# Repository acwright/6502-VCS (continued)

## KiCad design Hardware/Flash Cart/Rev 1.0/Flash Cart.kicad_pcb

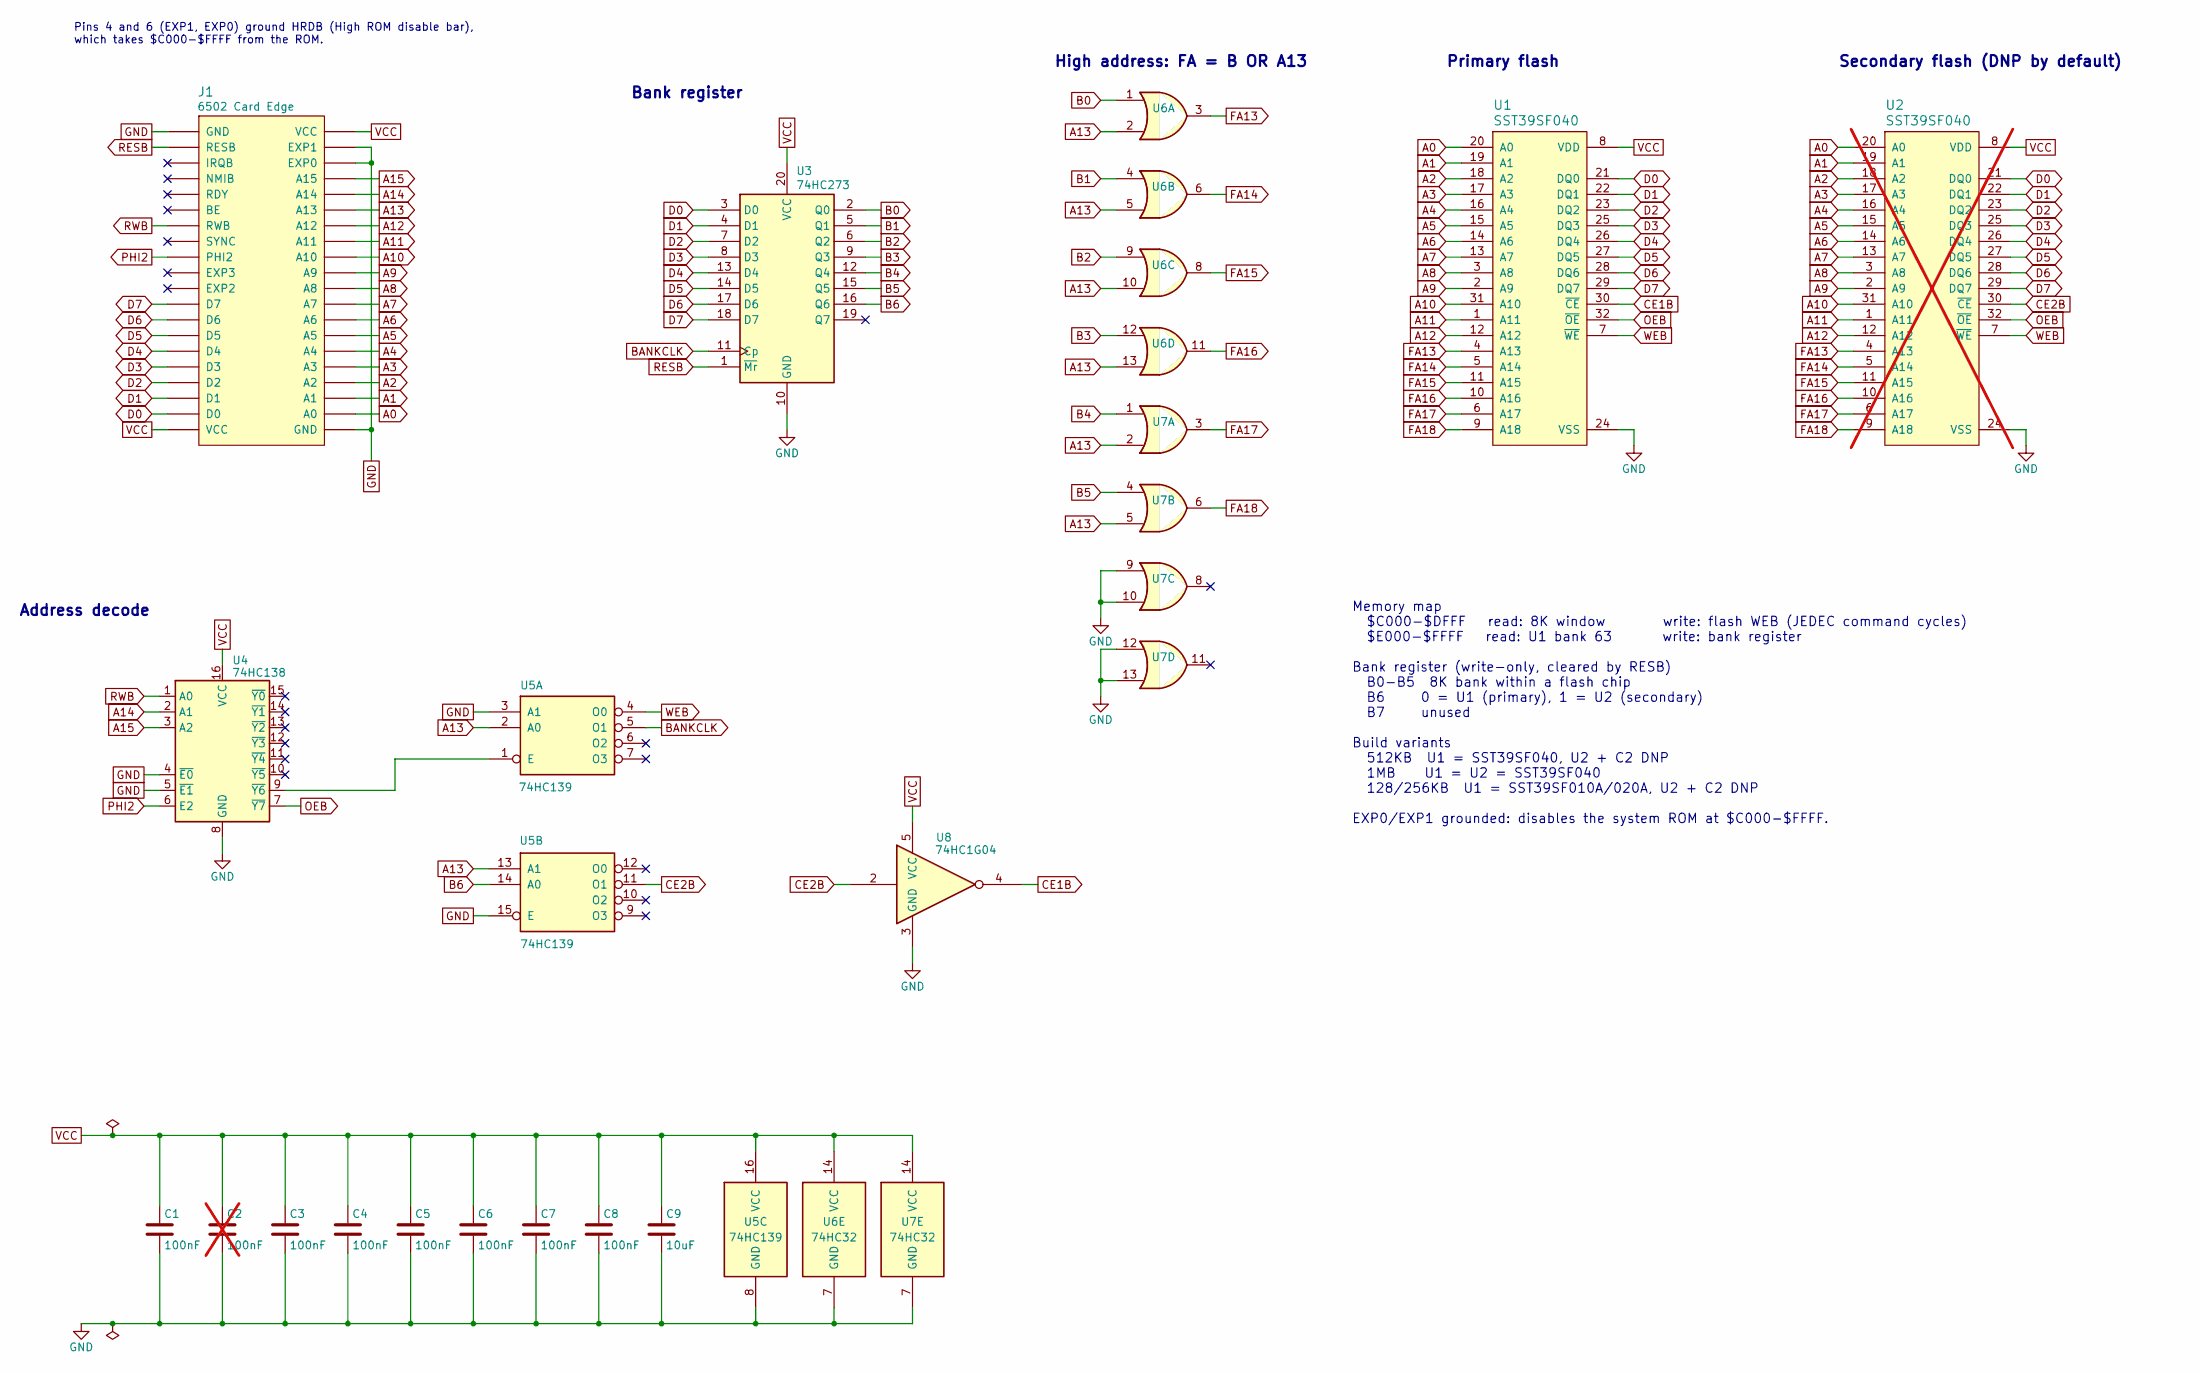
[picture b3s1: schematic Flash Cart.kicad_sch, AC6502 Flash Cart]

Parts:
C1, C3, C4, C5, C6, C7, C8: 100nF; C_0603_1608Metric; Digikey 399-C0603C104K5RACTUCT-ND
C2: 100nF; C_0603_1608Metric; Digikey 399-C0603C104K5RACTUCT-ND; not fitted
C9: 10uF; C_0805_2012Metric; Digikey 311-3502-1-ND
J1: 6502 Card Edge
U1: SST39SF040; TSOP-I-32_11.8x8mm_P0.5mm; Digikey 150-SST39SF040-70-4C-TU-ND
U2: SST39SF040; TSOP-I-32_11.8x8mm_P0.5mm; Digikey 150-SST39SF040-70-4C-TU-ND; not fitted
U3: 74HC273; SOIC-20W_7.5x12.8mm_P1.27mm; Digikey 1727-2795-1-ND
U4: 74HC138; SOIC-16_3.9x9.9mm_P1.27mm; Digikey 1727-2781-1-ND
U5: 74HC139; SOIC-16_3.9x9.9mm_P1.27mm; Digikey 1727-5943-1-ND
U6, U7: 74HC32; SOIC-14_3.9x8.7mm_P1.27mm; Digikey 1727-2797-1-ND
U8: 74HC1G04; SOT-23-5; Digikey 1727-6034-1-ND

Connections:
A0: J1.A0, U1.20 (A0), U2.20 (A0)
A1: J1.A1, U1.19 (A1), U2.19 (A1)
A2: J1.A2, U1.18 (A2), U2.18 (A2)
A3: J1.A3, U1.17 (A3), U2.17 (A3)
A4: J1.A4, U1.16 (A4), U2.16 (A4)
A5: J1.A5, U1.15 (A5), U2.15 (A5)
A6: J1.A6, U1.14 (A6), U2.14 (A6)
A7: J1.A7, U1.13 (A7), U2.13 (A7)
A8: J1.A8, U1.3 (A8), U2.3 (A8)
A9: J1.A9, U1.2 (A9), U2.2 (A9)
A10: J1.A10, U1.31 (A10), U2.31 (A10)
A11: J1.A11, U1.1 (A11), U2.1 (A11)
A12: J1.A12, U1.12 (A12), U2.12 (A12)
A13: J1.A13, U5.2 (A0), U5.13 (A1), U6.2, U6.5, U6.10, U6.13, U7.2, U7.5
A14: J1.A14, U4.2 (A1)
A15: J1.A15, U4.3 (A2)
B0: U3.2 (Q0), U6.1
B1: U3.5 (Q1), U6.4
B2: U3.6 (Q2), U6.9
B3: U3.9 (Q3), U6.12
B4: U3.12 (Q4), U7.1
B5: U3.15 (Q5), U7.4
B6: U3.16 (Q6), U5.14 (A0)
BANKCLK: U3.11 (Cp), U5.5 (O1)
CE1B: U1.30 (~CE), U8.4
CE2B: U2.30 (~CE), U5.11 (O1), U8.2
D0: J1.D0, U1.21 (DQ0), U2.21 (DQ0), U3.3 (D0)
D1: J1.D1, U1.22 (DQ1), U2.22 (DQ1), U3.4 (D1)
D2: J1.D2, U1.23 (DQ2), U2.23 (DQ2), U3.7 (D2)
D3: J1.D3, U1.25 (DQ3), U2.25 (DQ3), U3.8 (D3)
D4: J1.D4, U1.26 (DQ4), U2.26 (DQ4), U3.13 (D4)
D5: J1.D5, U1.27 (DQ5), U2.27 (DQ5), U3.14 (D5)
D6: J1.D6, U1.28 (DQ6), U2.28 (DQ6), U3.17 (D6)
D7: J1.D7, U1.29 (DQ7), U2.29 (DQ7), U3.18 (D7)
FA13: U1.4 (A13), U2.4 (A13), U6.3
FA14: U1.5 (A14), U2.5 (A14), U6.6
FA15: U1.11 (A15), U2.11 (A15), U6.8
FA16: U1.10 (A16), U2.10 (A16), U6.11
FA17: U1.6 (A17), U2.6 (A17), U7.3
FA18: U1.9 (A18), U2.9 (A18), U7.6
GND: C1.2, C2.2, C3.2, C4.2, C5.2, C6.2, C7.2, C8.2, C9.2, J1.EXP0, J1.EXP1, J1.GND, U1.24 (VSS), U2.24 (VSS), U3.10 (GND), U4.4 (~E0), U4.5 (~E1), U4.8 (GND), U5.3 (A1), U5.8 (GND), U5.15 (E), U6.7 (GND), U7.7 (GND), U7.9, U7.10, U7.12, U7.13, U8.3 (GND)
unnamed: U4.9 (~Y6), U5.1 (E)
OEB: U1.32 (~OE), U2.32 (~OE), U4.7 (~Y7)
PHI2: J1.PHI2, U4.6 (E2)
RESB: J1.RESB, U3.1 (~Mr)
RWB: J1.RWB, U4.1 (A0)
VCC: C1.1, C2.1, C3.1, C4.1, C5.1, C6.1, C7.1, C8.1, C9.1, J1.VCC, U1.8 (VDD), U2.8 (VDD), U3.20 (VCC), U4.16 (VCC), U5.16 (VCC), U6.14 (VCC), U7.14 (VCC), U8.5 (VCC)
WEB: U1.7 (~WE), U2.7 (~WE), U5.4 (O0)

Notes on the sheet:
High address: FA = B OR A13
Secondary flash (DNP by default)
Address decode
Memory map $C000-$DFFF read: 8K window write: flash WEB (JEDEC command cycles) $E000-$FFFF read: U1 bank 63 write: bank register Bank register (write-only, cleared by RESB) B0-B5 8K bank within a flash chip B6 0 = U1 (primary), 1 = U2 (secondary) B7 unused Build variants 512KB U1 = SST39SF040, U2 +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
Primary flash
Bank register
Pins 4 and 6 (EXP1, EXP0) ground HRDB (High ROM disable bar), which takes $C000-$FFFF from the ROM.

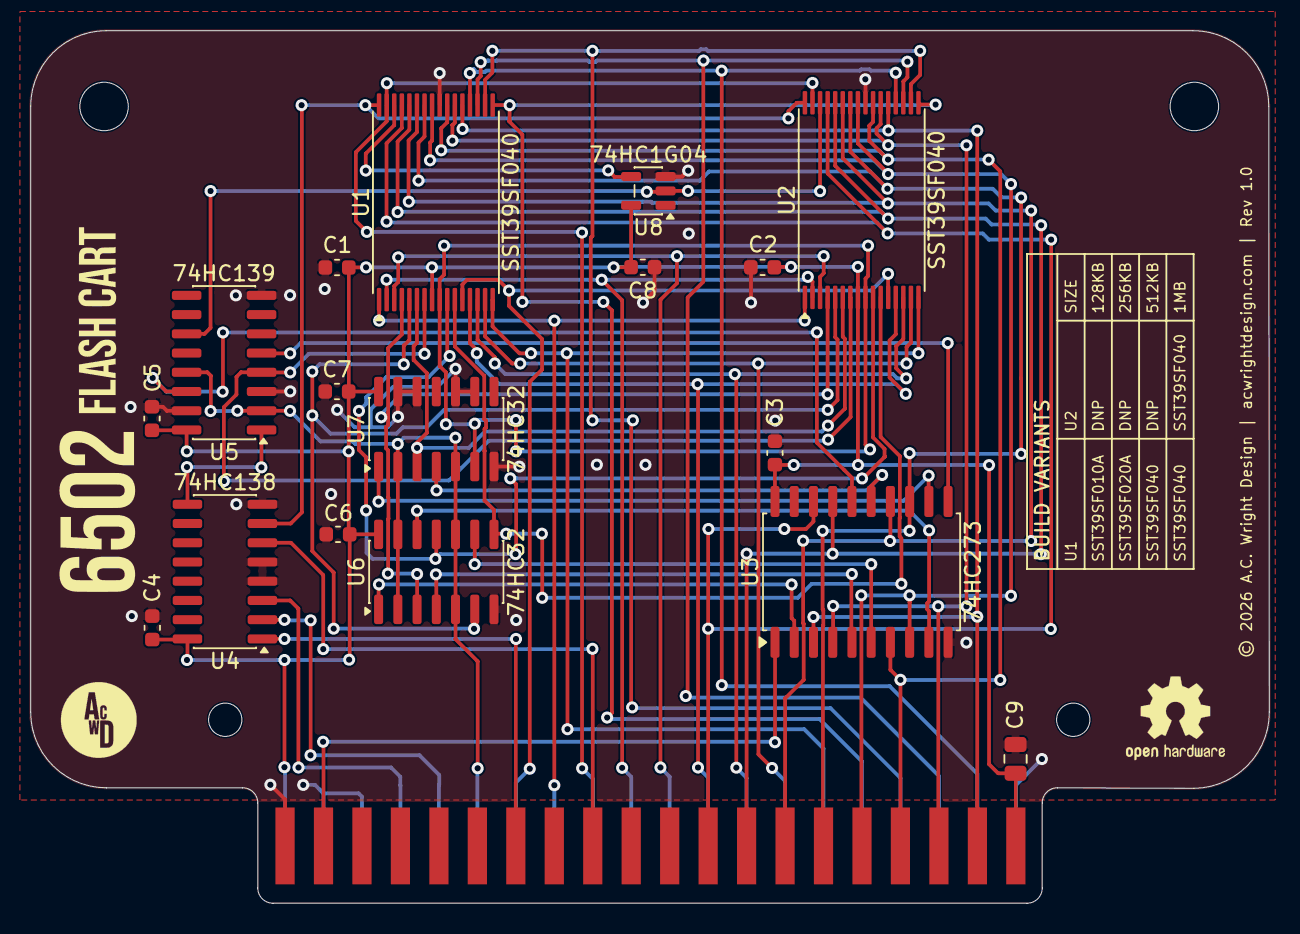
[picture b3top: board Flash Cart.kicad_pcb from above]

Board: 2 copper layers, 81.8 x 57.6 mm, 22 parts (0 on the bottom side), 48 nets.

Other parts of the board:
H1, H2: MountingHole; MountingHole_3.2mm_M3
H3, H4: MountingHole; MountingHole_2.2mm_M2

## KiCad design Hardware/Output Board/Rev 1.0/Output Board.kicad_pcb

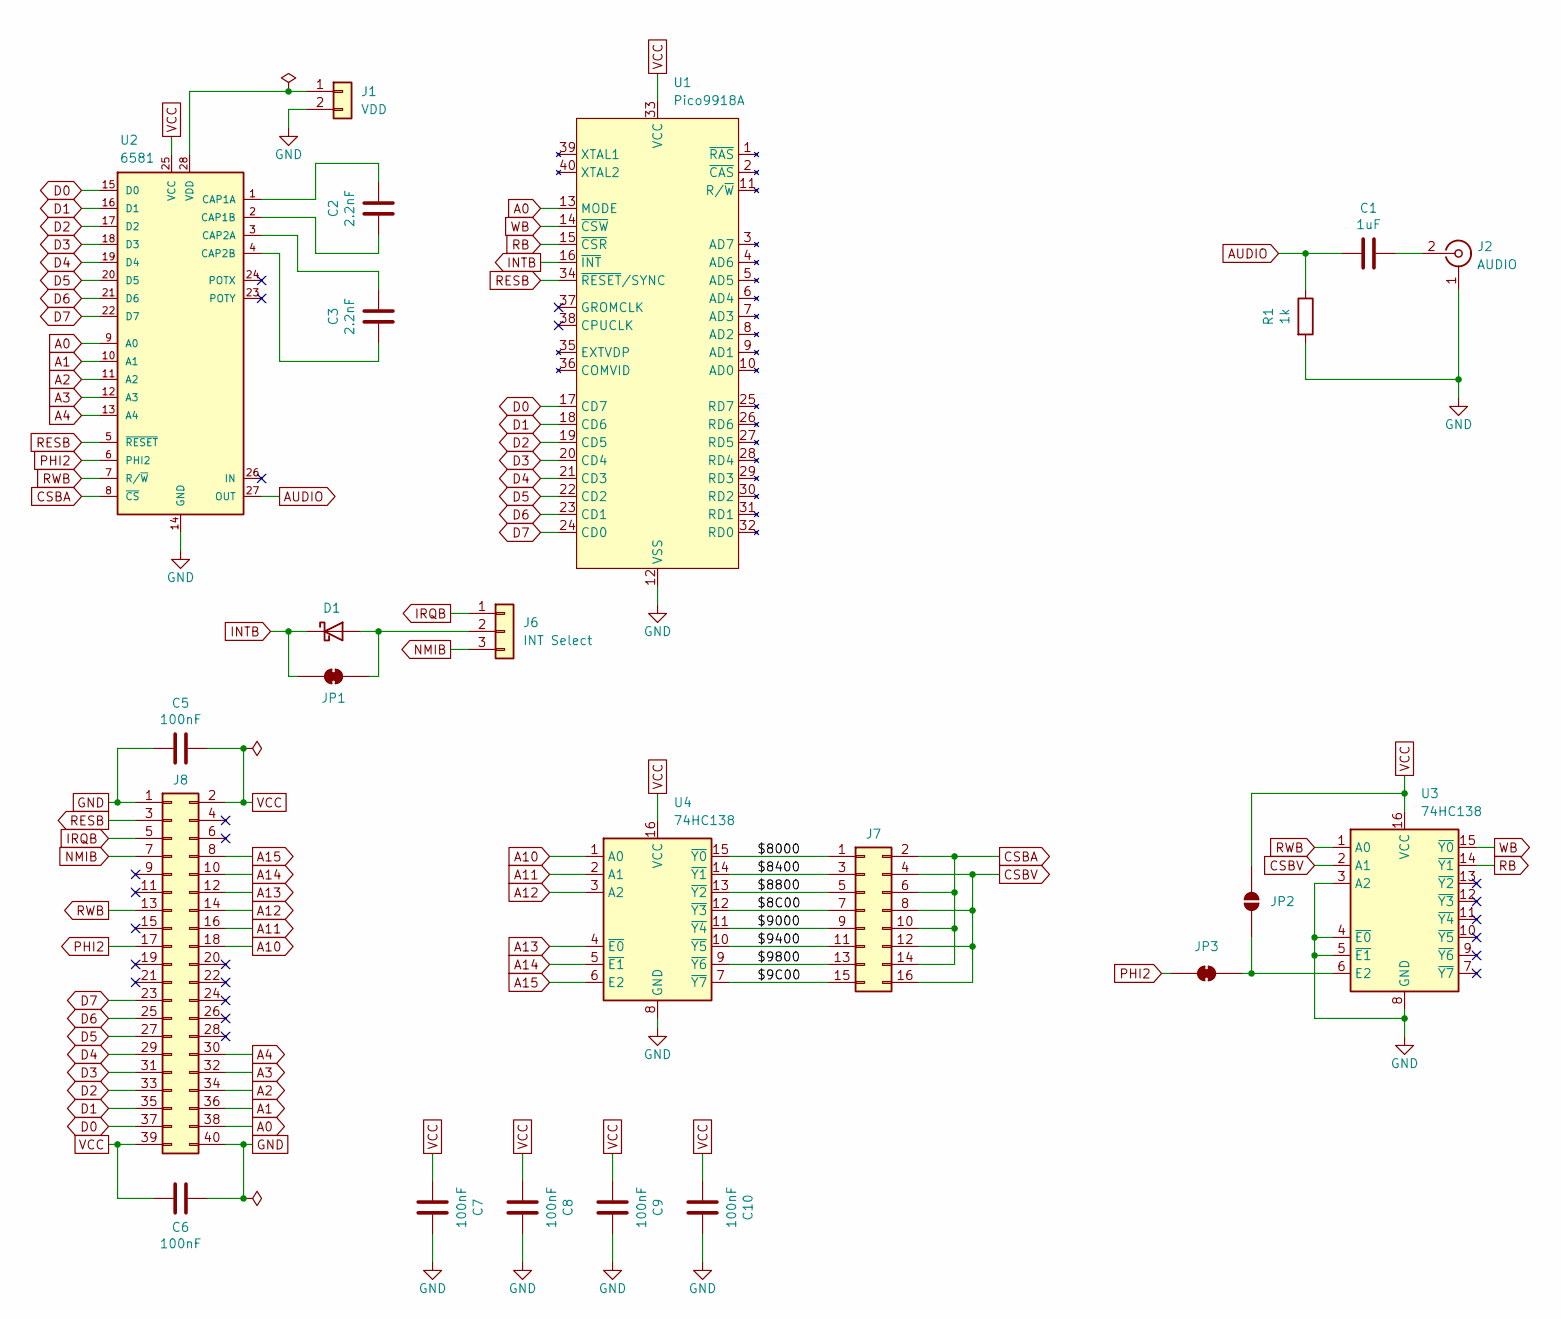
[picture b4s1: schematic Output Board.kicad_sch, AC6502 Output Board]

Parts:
C1: 1uF; C_0805_2012Metric; LCSC C28323
C2, C3: 2.2nF; C_0805_2012Metric; LCSC C28260
C5, C6, C7, C8, C9, C10: 100nF; C_0805_2012Metric; LCSC C49678
D1: 1N914; D_DO-35_SOD27_P7.62mm_Horizontal; Mouser 512-1N914
J1: VDD; JST_XH_B2B-XH-A_1x02_P2.50mm_Vertical; Digikey 455-B2B-XH-A-ND
J2: AUDIO; RCA Jack White; Digikey PJRAN1X1U02X-ND
J6: INT Select; PinHeader_1x03_P2.54mm_Vertical; Mouser 200-TSW14007TS
J7: IO SELECT; PinHeader_2x08_P2.54mm_Vertical; Mouser 649-67996-140HLF
J8: 6502 Bus; 6502 Bus Connector; Mouser 710-61204021621
JP1, JP3: SolderJumper_2_Bridged; SolderJumper-2_P1.3mm_Bridged_RoundedPad1.0x1.5mm
JP2: SolderJumper_2_Open; SolderJumper-2_P1.3mm_Open_RoundedPad1.0x1.5mm
R1: 1k; R_0805_2012Metric; LCSC C17513
U1: Pico9918A; DIP_Socket-40_W11.9mm_W12.7mm_W15.24mm_W17.78mm_W18.5mm_3M_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
U2: 6581; DIP_Socket-28_W11.9mm_W12.7mm_W15.24mm_W17.78mm_W18.5mm_3M_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
U3, U4: 74HC138; SOIC-16_3.9x9.9mm_P1.27mm; LCSC C5602

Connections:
/$8C00: J7.7, U4.12 (~Y3)
/$9C00: J7.15, U4.7 (~Y7)
/$8000: J7.1, U4.15 (~Y0)
/$8400: J7.3, U4.14 (~Y1)
/$8800: J7.5, U4.13 (~Y2)
/$9000: J7.9, U4.11 (~Y4)
/$9400: J7.11, U4.10 (~Y5)
/$9800: J7.13, U4.9 (~Y6)
A0: J8.38, U1.13 (MODE), U2.9 (A0)
A1: J8.36, U2.10 (A1)
A2: J8.34, U2.11 (A2)
A3: J8.32, U2.12 (A3)
A4: J8.30, U2.13 (A4)
A10: J8.18, U4.1 (A0)
A11: J8.16, U4.2 (A1)
A12: J8.14, U4.3 (A2)
A13: J8.12, U4.4 (~E0)
A14: J8.10, U4.5 (~E1)
A15: J8.8, U4.6 (E2)
AUDIO: C1.1, R1.1, U2.27 (OUT)
CSBA: J7.2, J7.6, J7.10, J7.14, U2.8 (~CS)
CSBV: J7.4, J7.8, J7.12, J7.16, U3.2 (A1)
D0: J8.37, U1.17 (CD7), U2.15 (D0)
D1: J8.35, U1.18 (CD6), U2.16 (D1)
D2: J8.33, U1.19 (CD5), U2.17 (D2)
D3: J8.31, U1.20 (CD4), U2.18 (D3)
D4: J8.29, U1.21 (CD3), U2.19 (D4)
D5: J8.27, U1.22 (CD2), U2.20 (D5)
D6: J8.25, U1.23 (CD1), U2.21 (D6)
D7: J8.23, U1.24 (CD0), U2.22 (D7)
GND: C5.2, C6.1, C7.2, C8.2, C9.2, C10.2, J1.2, J2.1 (Ext), J8.1, J8.40, R1.2, U1.12 (VSS), U2.14 (GND), U3.3 (A2), U3.4 (~E0), U3.5 (~E1), U3.8 (GND), U4.8 (GND)
INTB: D1.1 (K), JP1.1 (A), U1.16 (~INT)
IRQB: J6.1, J8.5
NMIB: J6.3, J8.7
unnamed: D1.2 (A), J6.2, JP1.2 (B)
unnamed: J1.1, U2.28 (VDD)
unnamed: C1.2, J2.2 (In)
unnamed: JP2.2 (B), JP3.1 (A), U3.6 (E2)
unnamed: C2.2, U2.1 (CAP1A)
unnamed: C2.1, U2.2 (CAP1B)
unnamed: C3.2, U2.3 (CAP2A)
unnamed: C3.1, U2.4 (CAP2B)
PHI2: J8.17, JP3.2 (B), U2.6 (PHI2)
RB: U1.15 (~CSR), U3.14 (~Y1)
RESB: J8.3, U1.34 (~RESET/SYNC), U2.5 (~RESET)
RWB: J8.13, U2.7 (R/~W), U3.1 (A0)
VCC: C5.1, C6.2, C7.1, C8.1, C9.1, C10.1, J8.2, J8.39, JP2.1 (A), U1.33 (VCC), U2.25 (VCC), U3.16 (VCC), U4.16 (VCC)
WB: U1.14 (~CSW), U3.15 (~Y0)

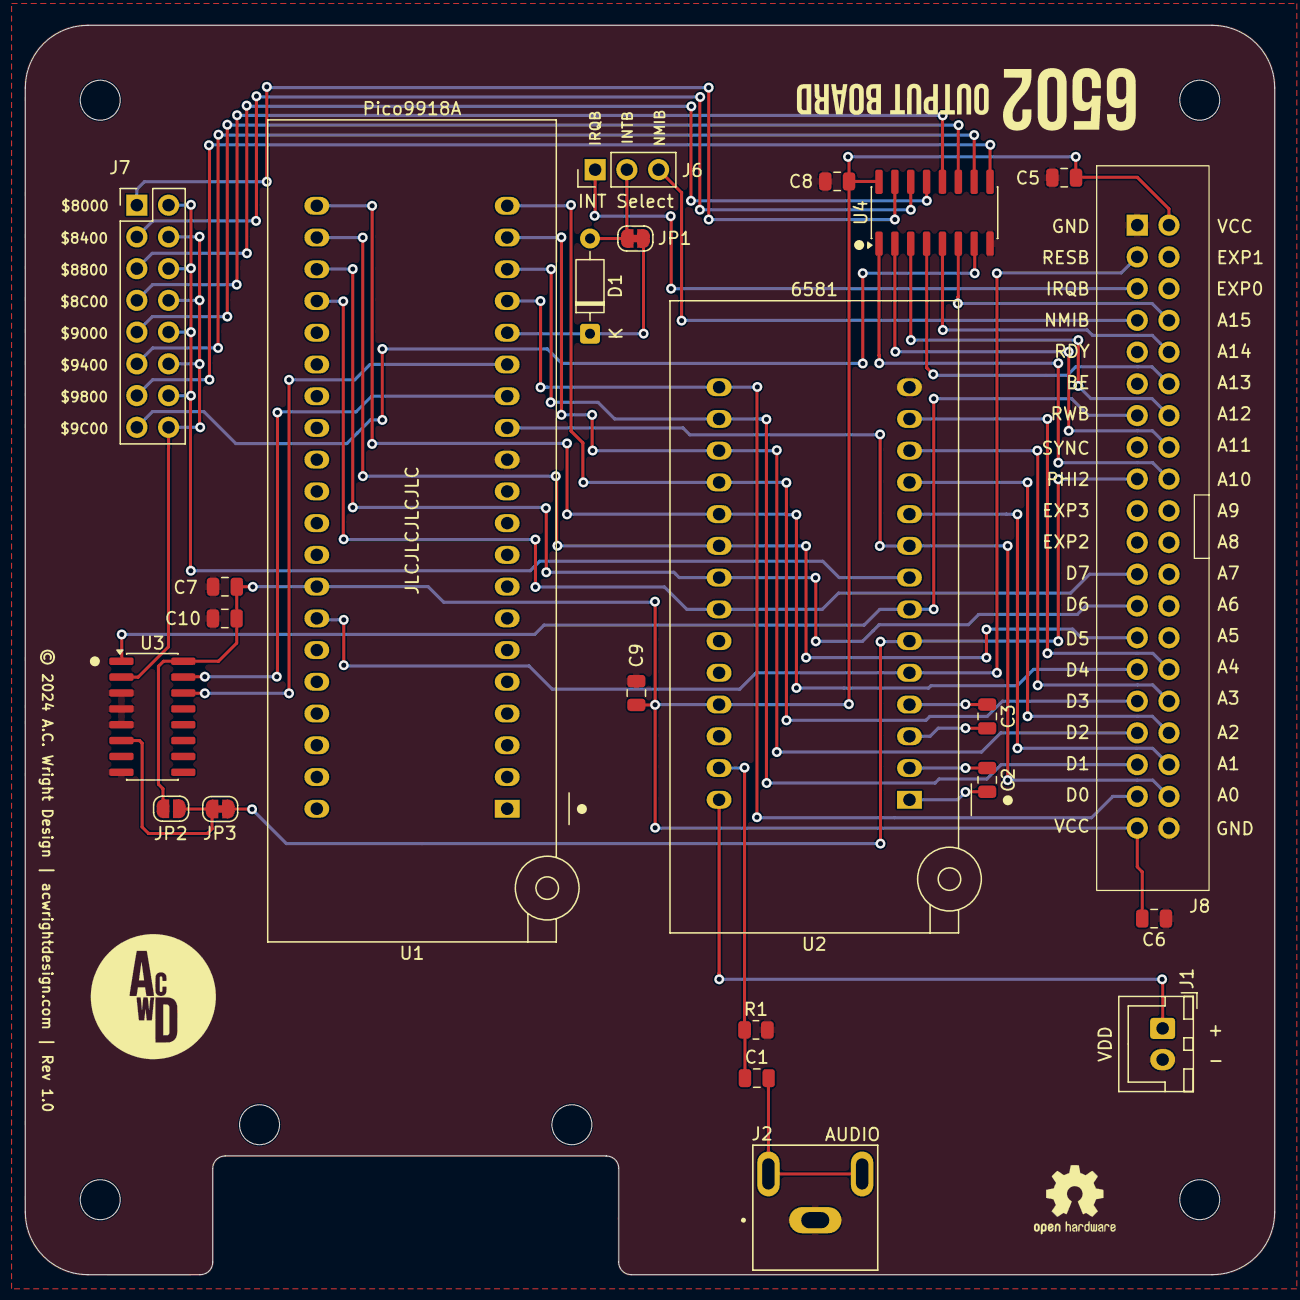
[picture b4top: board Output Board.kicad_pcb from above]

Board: 2 copper layers, 100.0 x 100.0 mm, 27 parts (0 on the bottom side), 48 nets.

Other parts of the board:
H1, H2, H3, H4: MountingHole; MountingHole_3.2mm_M3

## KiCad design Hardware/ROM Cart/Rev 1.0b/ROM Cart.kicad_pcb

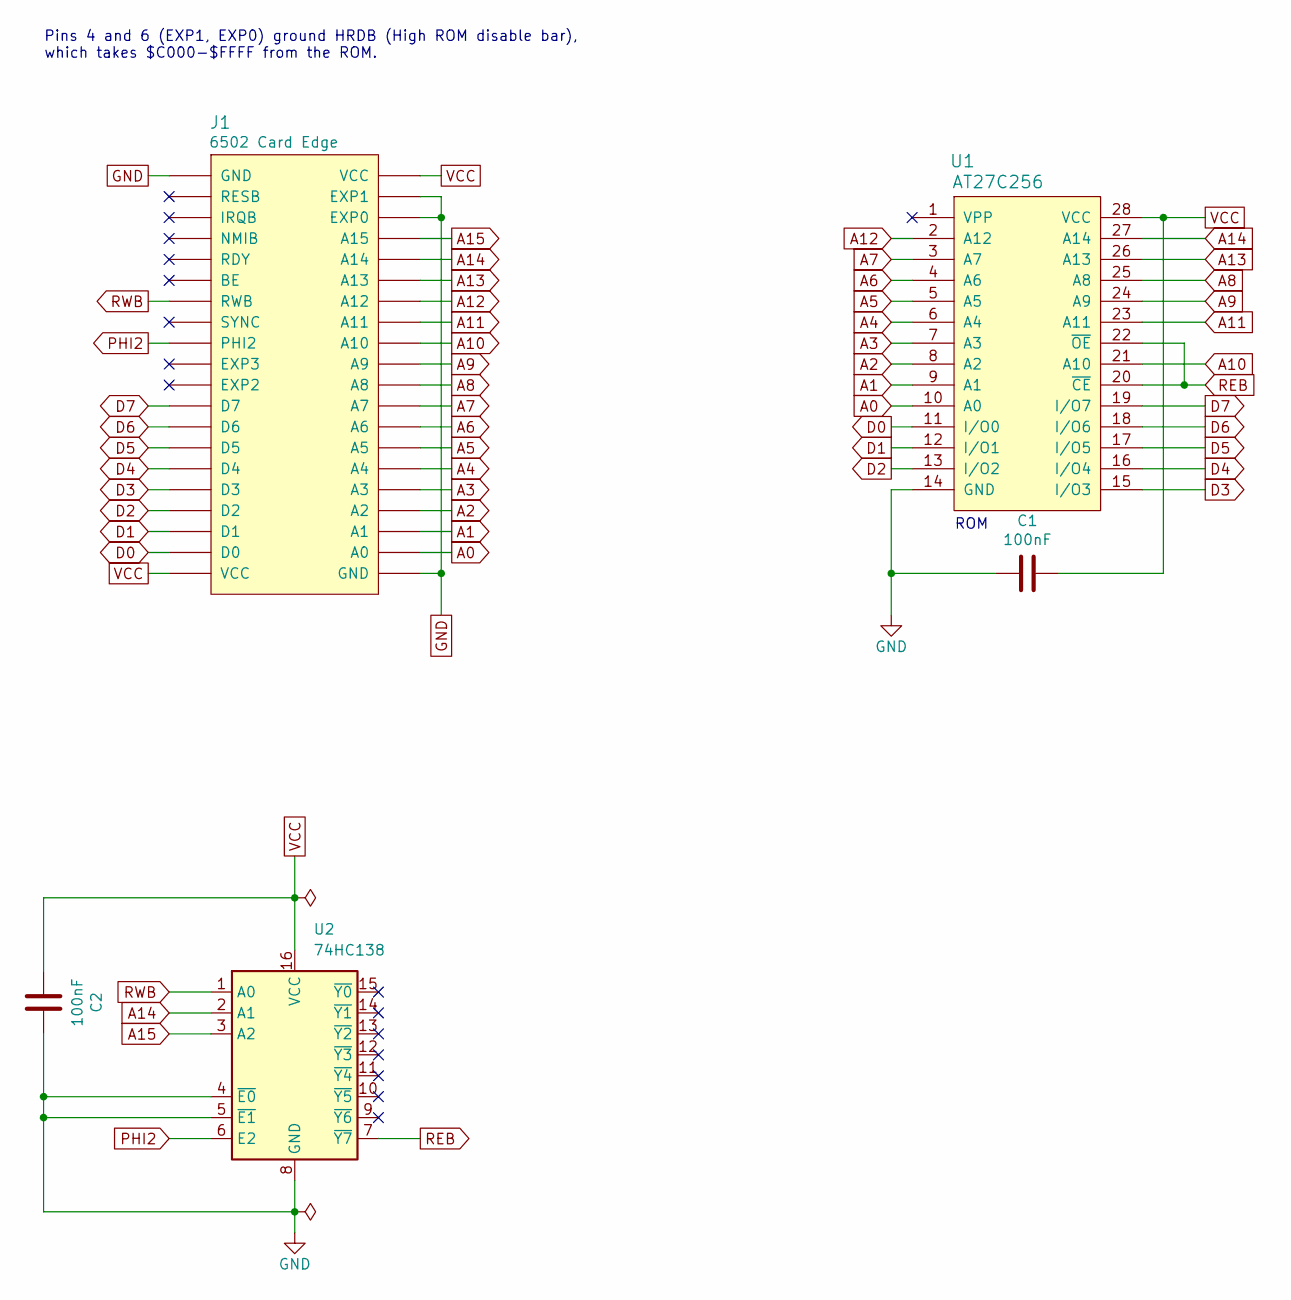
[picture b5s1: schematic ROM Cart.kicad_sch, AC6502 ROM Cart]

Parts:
C1, C2: 100nF; C_Disc_D5.0mm_W2.5mm_P5.00mm; Digikey 478-3188-ND
J1: 6502 Card Edge
U1: AT27C256; DIP-28_W15.24mm_Socket_LongPads; Digikey AT27C256R-70PU-ND
U2: 74HC138; DIP-16_W7.62mm_Socket_LongPads; Digikey 296-1575-5-ND

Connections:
A0: J1.A0, U1.10 (A0)
A1: J1.A1, U1.9 (A1)
A2: J1.A2, U1.8 (A2)
A3: J1.A3, U1.7 (A3)
A4: J1.A4, U1.6 (A4)
A5: J1.A5, U1.5 (A5)
A6: J1.A6, U1.4 (A6)
A7: J1.A7, U1.3 (A7)
A8: J1.A8, U1.25 (A8)
A9: J1.A9, U1.24 (A9)
A10: J1.A10, U1.21 (A10)
A11: J1.A11, U1.23 (A11)
A12: J1.A12, U1.2 (A12)
A13: J1.A13, U1.26 (A13)
A14: J1.A14, U1.27 (A14), U2.2 (A1)
A15: J1.A15, U2.3 (A2)
D0: J1.D0, U1.11 (I/O0)
D1: J1.D1, U1.12 (I/O1)
D2: J1.D2, U1.13 (I/O2)
D3: J1.D3, U1.15 (I/O3)
D4: J1.D4, U1.16 (I/O4)
D5: J1.D5, U1.17 (I/O5)
D6: J1.D6, U1.18 (I/O6)
D7: J1.D7, U1.19 (I/O7)
GND: C1.2, C2.2, J1.EXP0, J1.EXP1, J1.GND, U1.14 (GND), U2.4 (~E0), U2.5 (~E1), U2.8 (GND)
PHI2: J1.PHI2, U2.6 (E2)
REB: U1.20 (~CE), U1.22 (~OE), U2.7 (~Y7)
RWB: J1.RWB, U2.1 (A0)
VCC: C1.1, C2.1, J1.VCC, U1.28 (VCC), U2.16 (VCC)

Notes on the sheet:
ROM
Pins 4 and 6 (EXP1, EXP0) ground HRDB (High ROM disable bar), which takes $C000-$FFFF from the ROM.

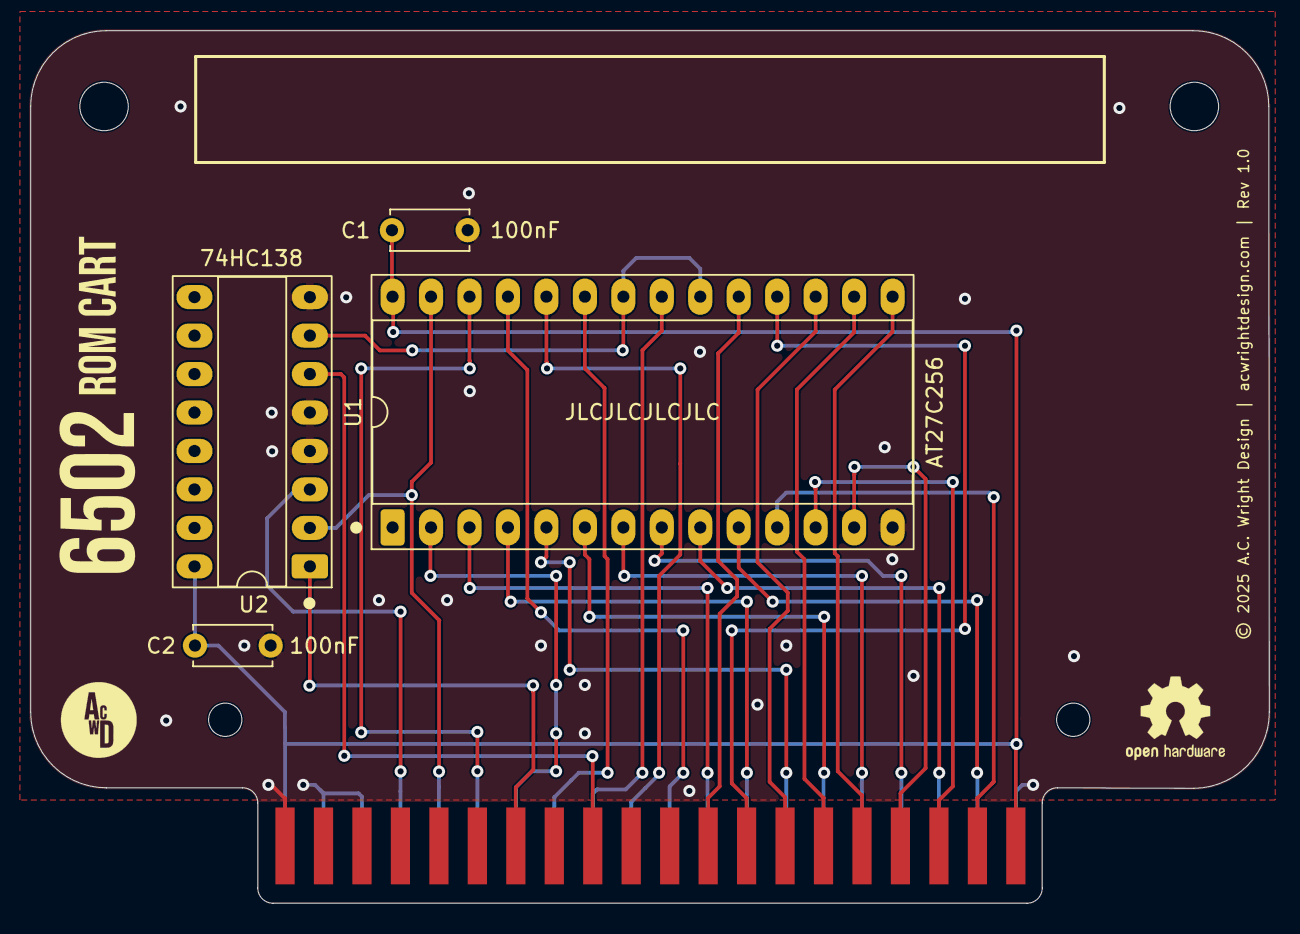
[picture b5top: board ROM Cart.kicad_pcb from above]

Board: 2 copper layers, 81.8 x 57.6 mm, 9 parts (0 on the bottom side), 29 nets.

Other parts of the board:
H1, H2: MountingHole; MountingHole_3.2mm_M3
H3, H4: MountingHole; MountingHole_2.2mm_M2

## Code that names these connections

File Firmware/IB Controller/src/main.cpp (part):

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// ============================================================================
// Keyboard Matrix Mapping 
// ============================================================================
// Rows: PA0-PA7 (VIA Port A)
// Columns: PB0-PB7 (VIA Port B)
//
//      PB0    PB1    PB2    PB3    PB4    PB5    PB6    PB7
// PA0:  `      1      2      3      4      5      6      7
// PA1:  8      9      0      -      =      BS     ESC    TAB
// PA2:  q      w      e      r      t      y      u      i
// PA3:  o      p      [      ]      \      INS    CAPS   a
// PA4:  s      d      f      g      h      j      k      l
// PA5:  ;      '      ENTER  DEL    SHIFT  z      x      c
// PA6:  v      b      n      m      ,      .      /      UP
// PA7:  CTRL   GUI    ALT    SPACE  FN     LEFT   DOWN   RIGHT
//
// Notes:
// - BS = Backspace (0x08), ESC = Escape (0x1B), TAB (0x09)
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
#define VIA_CA1 8
#define VIA_CA2 9
#define PS2CLK  10
#define PS2DATA 11

// PS2CLK (D10) is PD2, read straight from the register in the clock
// interrupt. If PS2CLK ever moves, this must move with it.
#define PS2CLK_IS_HIGH() (PIND & _BV(PD2))
#define VIA_CB1 12
#define VIA_CB2 13

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// Joystick State
// ============================================================================
// The two sticks share the sixteen VIA port lines with the key matrix:
// JOYSTICK A on PA0-PA7 (the matrix rows) and JOYSTICK B on PB0-PB7 (the
// columns). Every signal is active low -- the switches close to ground -- so an
// untouched stick leaves its lines pulled high.
//
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// ============================================================================
// VIA Port Access
// ============================================================================
// On the MightyCore "standard" pinout VIA_PA0-PA7 are D24-D31, which is exactly
// ATmega PORTA bits 0-7, and VIA_PB0-PB7 are D0-D7, which is exactly PORTB bits
// 0-7. Nothing else on this board lives on either register, so the whole port
// can be manipulated in a single instruction.
//
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// ports are wired to each other through the key switches, so anything driven
// on one can show up on the other.

// CA2 (PD1) and CB2 (PD5) are the 6502 asking for a port back, active high.
#define CA2_RELEASE_REQUESTED() (PIND & _BV(PD1))
#define CB2_RELEASE_REQUESTED() (PIND & _BV(PD5))

// CA1 (PD0) and CB1 (PD4) are the strobes. The VIA raises the flag on the
// falling edge (Kernal InitKB sets both to negative edge).
#define CA1_STROBE _BV(PD0)
#define CB1_STROBE _BV(PD4)

// How long a line left to its pull-up is given to rise before it is read. Sized
// for the weak case -- a port with no external pull-up, charging the bus and a
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// Maps each matrix position [row][col] to its base ASCII code (no modifiers)
// Special values: 0xFF = no key, 0xFE = modifier key (handled separately)
const uint8_t matrixMap[8][8] PROGMEM = {
  // PA0/Row 0: PB0    PB1    PB2    PB3    PB4    PB5    PB6    PB7
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  // PA1/Row 1
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  // PA2/Row 2
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  // PA3/Row 3
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  // PA4/Row 4
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  // PA5/Row 5
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  // PA6/Row 6
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  // PA7/Row 7
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};

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  pinMode(VIA_CA2, INPUT_PULLUP);
  pinMode(VIA_CB1, OUTPUT);
  pinMode(VIA_CB2, INPUT_PULLUP);
  pinMode(PS2CLK, INPUT_PULLUP);
  pinMode(PS2DATA, INPUT_PULLUP);

  digitalWrite(VIA_CA1, HIGH);
  digitalWrite(VIA_CB1, HIGH);
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  idlePort(PS2_PORT);
  idlePort(MATRIX_PORT);

  attachInterrupt(digitalPinToInterrupt(PS2CLK), onInterrupt, FALLING);

}

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
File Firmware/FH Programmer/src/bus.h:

// The two bus primitives, and nothing above them knows about flash.
//
// The Flash Helper is an Arduino Mega 2560 R3 shield that pretends to be a
// 65C02 on the far side of a cartridge slot (6502-VCS PLAN.md §5).  Everything
// it can do is built out of one read cycle and one write cycle, both of them
// here.
//
// The pin allocation is fixed by the Rev 1.0 schematic.  Three whole ports and
// five single lines, chosen so that the address and the data buses are single
// byte port writes with no bit shuffling:
//
//   PORTA   D22-D29   D0-D7, the data bus          (PA0 = D0)
//   PORTC   D37-D30   A8-A15                       (PC0 = A8; the header runs backwards)
//   PORTL   D49-D42   A0-A7                        (PL0 = A0; likewise)
//   PB7     D13       PHI2                         (also the on-board LED)
//   PB5     D11       RWB
//   PG5     D4        RESB
//   PE4/PE5 D2/D3     IRQB/NMIB - never driven here; they are for the card tester
//
// PLAN.md §5.3 and this project's README both describe the data bus as PORTL.
// That is a slip in the prose: the schematic puts D0-D7 on PORTA and A0-A7 on
// PORTL, and this file follows the schematic.

#pragma once

#include <stdint.h>

/** Take the bus, park it idle, and pulse RESB so the cart's bank register is 0. */
void bus_begin();

/** One write cycle. `addr` is a CPU address; the cart decodes $C000-$FFFF. */
void bus_write(uint16_t addr, uint8_t data);

/** One read cycle. */
uint8_t bus_read(uint16_t addr);

/** Pulse RESB low. This is what clears the cart's bank register to 0. */
void bus_reset_pulse();

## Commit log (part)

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2026-05-03 Cleanup VCS project
2026-05-04 Finish VCS cleanup
2026-05-04 README fix
2026-05-16 Add BOMs
2026-05-19 Finish BOM and add to README
2026-05-19 Restore exclude from BOM
2026-06-15 Change pull up resistor values
2026-06-16 Remove BOM CSV's
2026-06-18 Add Main Board Rev 1.1
